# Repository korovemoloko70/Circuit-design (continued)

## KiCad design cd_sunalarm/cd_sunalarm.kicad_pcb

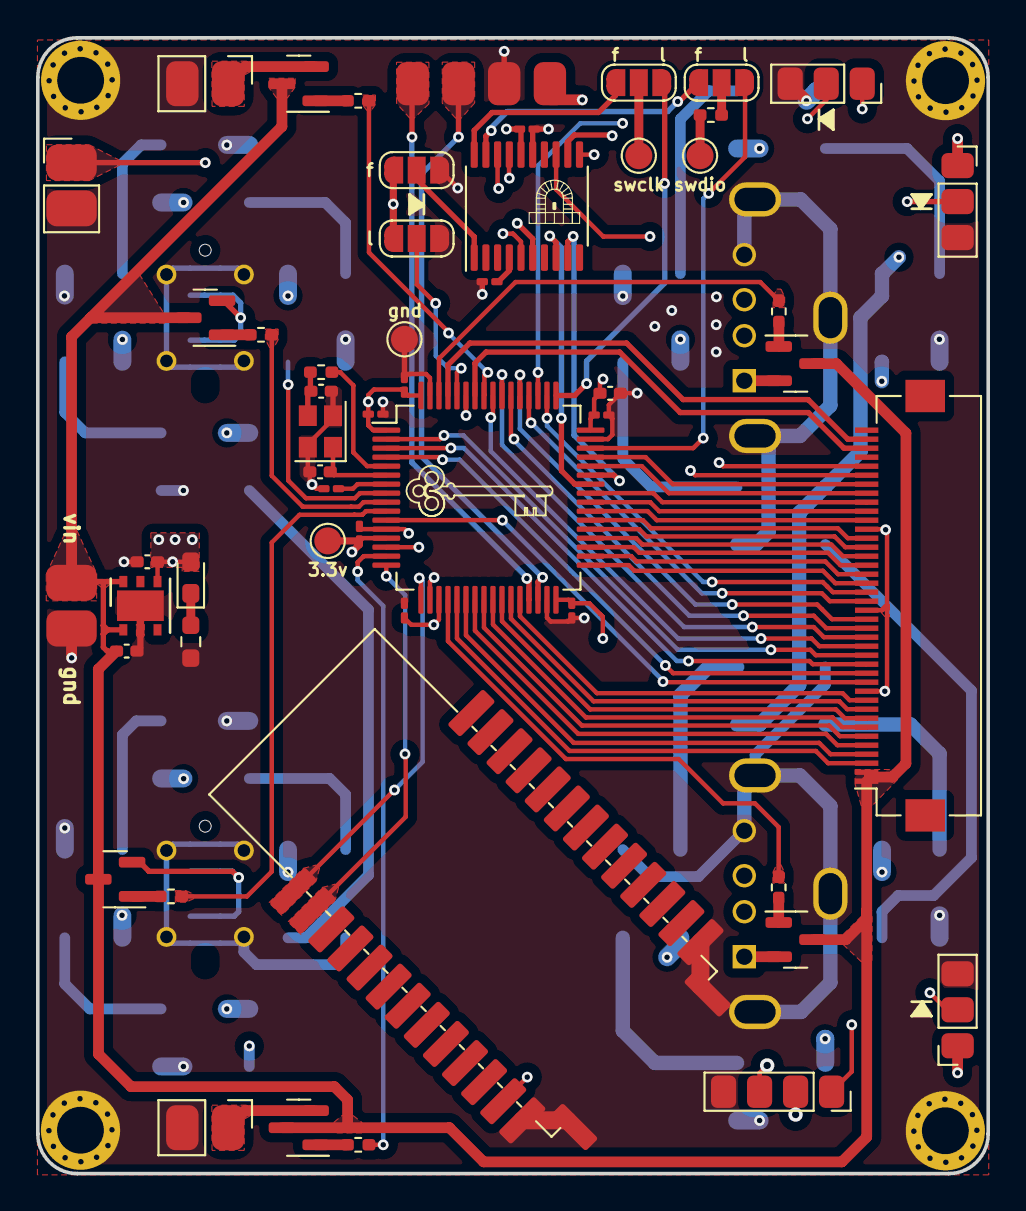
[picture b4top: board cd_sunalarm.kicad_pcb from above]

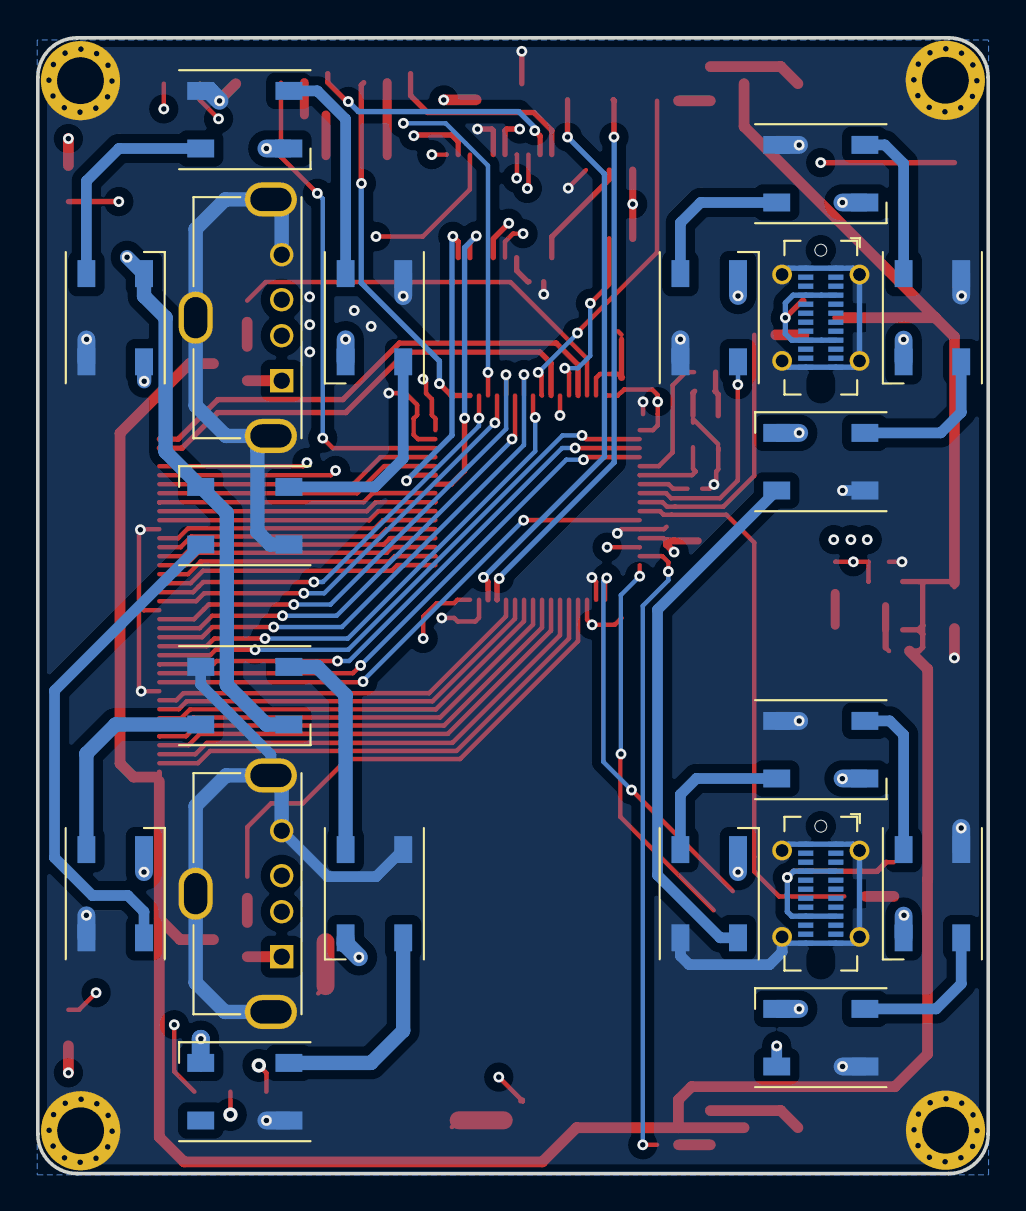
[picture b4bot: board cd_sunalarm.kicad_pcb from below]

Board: 4 copper layers, 52.8 x 63.1 mm, 73 parts (20 on the bottom side), 98 nets.

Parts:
C1: 4u7; C_0402_1005Metric_Pad0.74x0.62mm_HandSolder
C2, C4: 12p; C_0402_1005Metric_Pad0.74x0.62mm_HandSolder
C3, C5, C6, C7, C8, C9, C11, C12, C13: 100nF; C_0201_0603Metric_Pad0.64x0.40mm_HandSolder
C15, C16: 1uF; C_0402_1005Metric_Pad0.74x0.62mm_HandSolder
D1, D2, D3, D4, D5, D6, D7, D8, D9, D10, D11, D12, D13, D14, D15, D16: WS2812B; LED_SK6812_PLCC4_5.0x5.0mm_P3.2mm
D22: green; LED_0603_1608Metric_Pad1.05x0.95mm_HandSolder
J1: Display; Hirose_FH12-40S-0.5SH_1x40-1MP_P0.50mm_Horizontal
J2, J3, J12: Conn_01x03_Female; PinSocket_1x03_P2.00mm_Vertical
J4: temperature; PinSocket_1x04_P2.54mm_Vertical
J5, J6: USB_A; USB_A_Molex_105057_Vertical
J7: WiCh; PinHeader_1x02_P2.54mm_Vertical
J8: Dif; PinHeader_1x02_P2.54mm_Vertical
J9: LED; PinHeader_1x02_P2.54mm_Vertical
J10: power; PinSocket_1x02_P2.54mm_Vertical
J11: sound; PinSocket_1x04_P2.00mm_Vertical
JP1, JP2, JP3, JP4: SolderJumper_3_Open; SolderJumper-3_P1.3mm_Open_RoundedPad1.0x1.5mm
P1, P2: USB_C_Plug_USB2.0; USB_C_Receptacle_GCT_USB4115-03-C
Q2, Q3, Q4, Q5, Q6, Q7: Q_NPN_BEC; SOT-23
R1: 0; R_0402_1005Metric_Pad0.72x0.64mm_HandSolder
R3: 47; R_0402_1005Metric_Pad0.72x0.64mm_HandSolder
R8, R10, R11, R12, R13, R14: 220; R_0402_1005Metric_Pad0.72x0.64mm_HandSolder
R15: 1k; R_0603_1608Metric_Pad0.98x0.95mm_HandSolder
TP1, TP2, TP3, TP4: TestPoint_Small; TestPoint_Pad_D1.5mm
U1: STM32F031F4Px; TSSOP-20_4.4x6.5mm_P0.65mm
U2: STM32L476RCTx; LQFP-64_10x10mm_P0.5mm
U3: HM-10; Bluetooth
U4: LD39050PU33R; DFN-6-1EP_3x3mm_P0.95mm_EP1.7x2.6mm
Y1: 16MHz; Crystal_SMD_2520-4Pin_2.5x2.0mm

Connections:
+3V3: C1.1, C5.1, C6.1, C7.1, C9.1, C11.1, C12.1, C13.1, C16.1, D1.1 (VDD), D2.1 (VDD), D3.1 (VDD), D4.1 (VDD), D5.1 (VDD), D6.1 (VDD), D7.1 (VDD), D8.1 (VDD), D9.1 (VDD), D10.1 (VDD), D11.1 (VDD), D12.1 (VDD), D13.1 (VDD), D14.1 (VDD), D15.1 (VDD), D16.1 (VDD), D22.2 (A), J2.1, J3.1, J4.1, J12.1, JP3.1 (A), JP4.1 (A), TP1.1, U1.5 (VDDA), U1.16 (VDD), U2.1 (VBAT), U2.13 (VDDA), U2.19 (VDD), U2.32 (VDD), U2.48 (VDDUSB), U2.64 (VDD), U3.12 (VCC), U4.4 (VOUT)
+5V: C15.1, J1.1, J1.2, J10.1, Q2.3 (C), Q3.3 (C), Q4.3 (C), Q5.3 (C), Q6.3 (C), Q7.3 (C), U4.1 (EN), U4.6 (VIN)
/NRST_F: C3.1, U1.4 (NRST)
/NRST_L: C8.2, U2.7 (NRST)
B0: J1.21, U2.52 (PC11)
B1: J1.22, U2.50 (PA15)
B2: J1.23, U2.33 (PB12)
B3: J1.24, U2.34 (PB13)
B4: J1.25, U2.35 (PB14)
B5: J1.26, U2.36 (PB15)
B6: J1.27, U2.37 (PC6)
B7: J1.28, U2.38 (PC7)
BL_CTR: J1.34, U2.45 (PA12)
BOOT0_F: JP4.2 (C), U1.1 (BOOT0)
BOOT0_L: JP3.2 (C), U2.60 (BOOT0)
B_RX: U2.16 (PA2), U3.2 (UART_RX)
B_TX: U2.17 (PA3), U3.1 (UART_TX)
CTP_INT: J1.39, U2.61 (PB8)
CTP_RST: J1.35, U2.14 (PA0)
CTP_SCL: J1.38, U2.58 (PB6)
CTP_SDA: J1.36, U2.59 (PB7)
DCLK: J1.30, U2.39 (PC8)
DEN: J1.33, U2.44 (PA11)
DIN: D1.4 (DIN), U2.8 (PC0)
Dif: J8.1, Q2.2 (E)
G0: J1.12, U2.11 (PC3)
G1: J1.13, U2.4 (PC15)
G2: J1.14, U2.3 (PC14)
G3: J1.15, U2.2 (PC13)
G4: J1.16, U2.56 (PB4)
G5: J1.17, U2.55 (PB3)
G6: J1.18, U2.54 (PD2)
G7: J1.19, U2.53 (PC12)
GND: C1.2, C2.2, C3.2, C4.2, C5.2, C6.2, C7.2, C8.1, C9.2, C11.2, C12.2, C13.2, C15.2, C16.2, D1.3 (VSS), D2.3 (VSS), D3.3 (VSS), D4.3 (VSS), D5.3 (VSS), D6.3 (VSS), D7.3 (VSS), D8.3 (VSS), D9.3 (VSS), D10.3 (VSS), D11.3 (VSS), D12.3 (VSS), D13.3 (VSS), D14.3 (VSS), D15.3 (VSS), D16.3 (VSS), J1.11, J1.20, J1.29, J2.3, J3.3, J4.2, J5.4 (GND), J5.5 (Shield), J6.4 (GND), J6.5 (Shield), J7.2, J8.2, J9.2, J10.2, J11.4, J12.3, JP3.3 (B), JP4.3 (B), P1.A1 (GND), P1.A12 (GND), P1.B1 (GND), P1.B12 (GND), P1.S1 (SHIELD), P2.A1 (GND), P2.A12 (GND), P2.B1 (GND), P2.B12 (GND), P2.S1 (SHIELD), R15.2, TP2.1, U1.15 (VSS), U2.12 (VSSA), U2.18 (VSS), U2.31 (VSS), U2.47 (VSS), U2.63 (VSS), U3.13 (GND), U3.14 (GND), U3.21 (GND), U3.22 (GND), U4.2 (GND), U4.7, Y1.2, Y1.4
HSYNC: J1.31, U2.40 (PC9)
LED: J9.1, U1.6 (PA0)
L_IN: J11.3, U1.18 (PA10)
Light1: J2.2, U1.11 (PA5)
Light2: J3.2, U1.12 (PA6)
MIC: J12.2, U2.51 (PC10)
unnamed: C4.1, R3.2, Y1.3
unnamed: D1.2 (DOUT), D2.4 (DIN)
unnamed: D2.2 (DOUT), D3.4 (DIN)
unnamed: D3.2 (DOUT), D4.4 (DIN)
unnamed: D4.2 (DOUT), D5.4 (DIN)
unnamed: D5.2 (DOUT), D6.4 (DIN)
unnamed: D6.2 (DOUT), D7.4 (DIN)
unnamed: D7.2 (DOUT), D8.4 (DIN)
unnamed: D8.2 (DOUT), D9.4 (DIN)
unnamed: D10.2 (DOUT), D11.4 (DIN)
unnamed: D9.2 (DOUT), D10.4 (DIN)
unnamed: D11.2 (DOUT), D12.4 (DIN)
unnamed: D12.2 (DOUT), D13.4 (DIN)
unnamed: D13.2 (DOUT), D14.4 (DIN)
unnamed: D14.2 (DOUT), D15.4 (DIN)
unnamed: D15.2 (DOUT), D16.4 (DIN)
unnamed: D22.1 (K), R15.1
unnamed: JP1.2 (C), R1.2
unnamed: Q2.1 (B), R8.1
unnamed: Q3.1 (B), R10.1
unnamed: Q4.1 (B), R11.1
unnamed: Q5.1 (B), R12.1
unnamed: Q6.1 (B), R13.1
unnamed: Q7.1 (B), R14.1
OCS_IN: C2.1, U2.6 (PH1), Y1.1
OCS_OUT: R3.1, U2.5 (PH0)
R0: J1.3, U2.21 (PA5)
R1: J1.4, U2.22 (PA6)
R2: J1.5, U2.23 (PA7)
R3: J1.6, U2.24 (PC4)
R4: J1.7, U2.25 (PC5)
R5: J1.8, U2.26 (PB0)
R6: J1.9, U2.27 (PB1)
R7: J1.10, U2.28 (PB2)
RX1: U1.9 (PA3), U2.43 (PA10)
R_IN1: J11.1, U1.13 (PA7)
R_IN2: J11.2, U1.17 (PA9)
STMDif: R8.2, U2.57 (PB5)
STMWiCh: R14.2, U2.15 (PA1)
STMusbA1: R12.2, U2.62 (PB9)
STMusbA2: R13.2, U2.20 (PA4)
STMusbC1: R10.2, U2.10 (PC2)
STMusbC2: R11.2, U2.9 (PC1)
SWCLK: JP2.2 (C), TP4.1
SWCLK_F: JP2.1 (A), U1.20 (PA14)
SWCLK_L: JP2.3 (B), U2.49 (PA14)
SWDIO: R1.1, TP3.1
SWDIO_F: JP1.1 (A), U1.19 (PA13)
SWDIO_L: JP1.3 (B), U2.46 (PA13)
TX1: U1.8 (PA2), U2.42 (PA9)
T_SCL: J4.4, U2.29 (PB10)
T_SDA: J4.3, U2.30 (PB11)
VSYNC: J1.32, U2.41 (PA8)
WiCh: J7.1, Q7.2 (E)
usbA1: J5.1 (VBUS), Q5.2 (E)
usbA2: J6.1 (VBUS), Q6.2 (E)
usbC1: P1.A4 (VBUS), P1.A9 (VBUS), P1.B4 (VBUS), P1.B9 (VBUS), Q3.2 (E)
usbC2: P2.A4 (VBUS), P2.A9 (VBUS), P2.B4 (VBUS), P2.B9 (VBUS), Q4.2 (E)

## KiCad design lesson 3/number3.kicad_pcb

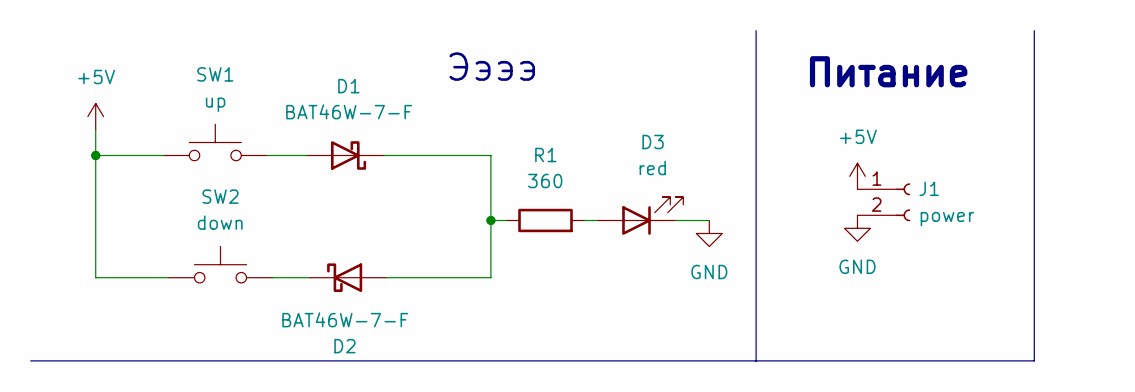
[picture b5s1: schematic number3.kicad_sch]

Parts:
D1, D2: BAT46W-7-F; Nexperia_CFP3_SOD-123W
D3: red; LED_0805_2012Metric_Pad1.15x1.40mm_HandSolder
J1: power; PinSocket_1x02_P2.54mm_Vertical
R1: 360; R_0805_2012Metric_Pad1.20x1.40mm_HandSolder
SW1: up; SW_SPST_TL3342
SW2: down; SW_SPST_TL3342

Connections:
+5V: J1.1, SW1.1, SW2.1
GND: D3.1 (K), J1.2
unnamed: D1.1 (K), D2.2 (A), R1.1
unnamed: D1.2 (A), SW1.2
unnamed: D2.1 (K), SW2.2
unnamed: D3.2 (A), R1.2

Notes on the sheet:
Питание
Ээээ

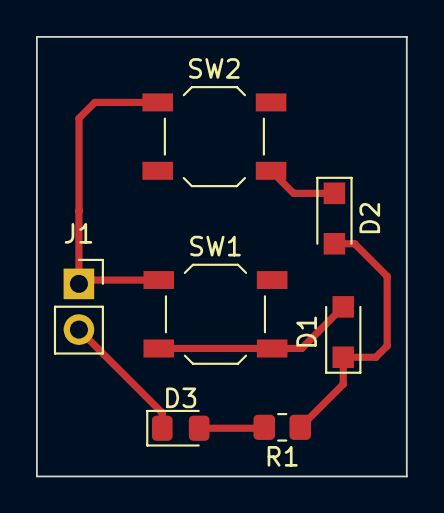
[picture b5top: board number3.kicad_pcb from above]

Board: 2 copper layers, 20.6 x 24.4 mm, 7 parts (0 on the bottom side), 6 nets.

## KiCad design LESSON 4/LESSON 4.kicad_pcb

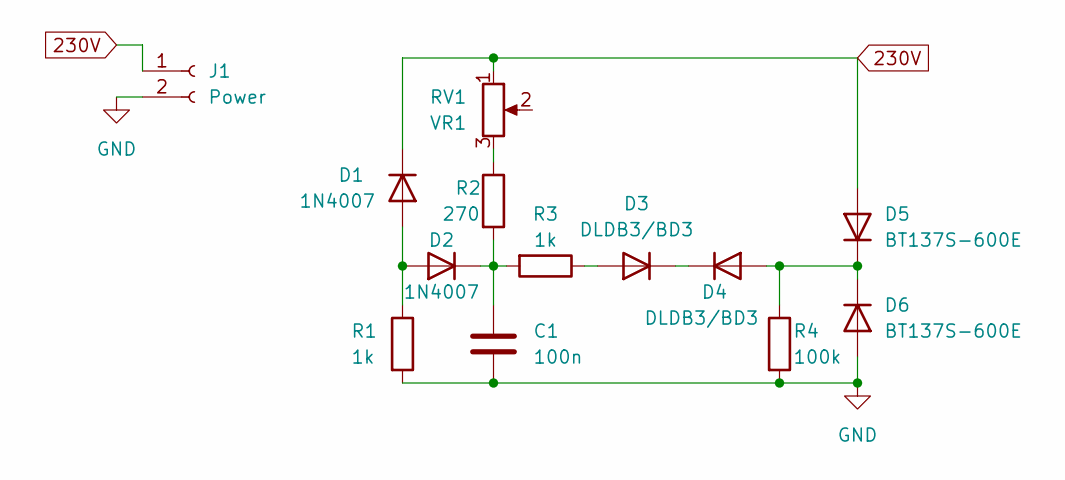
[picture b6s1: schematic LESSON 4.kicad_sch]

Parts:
C1: 100n; C_0805_2012Metric_Pad1.18x1.45mm_HandSolder
D1, D2: 1N4007; D_0603_1608Metric_Pad1.05x0.95mm_HandSolder
D3, D4: DLDB3/BD3; D_0603_1608Metric_Pad1.05x0.95mm_HandSolder
D5, D6: BT137S-600E; D_0603_1608Metric_Pad1.05x0.95mm_HandSolder
J1: Power; PinSocket_2x01_P2.54mm_Vertical
R1: 1k; R_0612_1632Metric_Pad1.18x3.40mm_HandSolder
R2: 270; R_0612_1632Metric_Pad1.18x3.40mm_HandSolder
R3: 1k; R_0603_1608Metric_Pad0.98x0.95mm_HandSolder
R4: 100k; R_01005_0402Metric_Pad0.57x0.30mm_HandSolder
RV1: VR1; Potentiometer_Bourns_3314R-1_Vertical_Hole

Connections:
230V: D1.1 (K), D5.2 (A), J1.1, RV1.1
GND: C1.2, D6.2 (A), J1.2, R1.2, R4.2
unnamed: C1.1, D2.1 (K), R2.2, R3.2
unnamed: D1.2 (A), D2.2 (A), R1.1
unnamed: D3.1 (K), D4.1 (K)
unnamed: D3.2 (A), R3.1
unnamed: D4.2 (A), D5.1 (K), D6.1 (K), R4.1
unnamed: R2.1, RV1.3

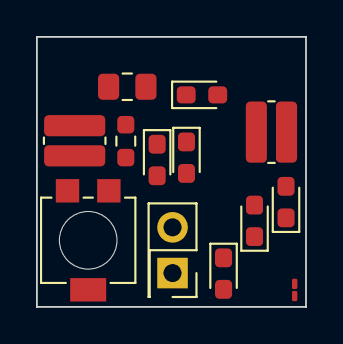
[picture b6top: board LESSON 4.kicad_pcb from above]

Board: 2 copper layers, 15.0 x 15.0 mm, 13 parts (0 on the bottom side), 8 nets.

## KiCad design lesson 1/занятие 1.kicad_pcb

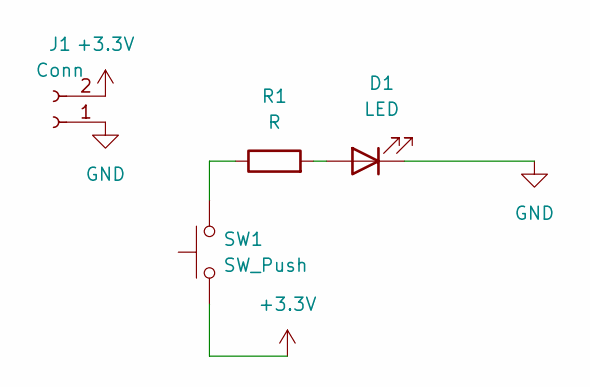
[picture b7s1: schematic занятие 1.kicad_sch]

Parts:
D1: LED; D_0603_1608Metric_Pad1.05x0.95mm_HandSolder
J1: Conn; PinSocket_2x01_P2.54mm_Vertical
R1: R; R_0805_2012Metric_Pad1.20x1.40mm_HandSolder
SW1: SW_Push; SW_SPST_TL3305B

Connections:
+3.3V: J1.2, SW1.1
GND: D1.1 (K), J1.1
unnamed: D1.2 (A), R1.2
unnamed: R1.1, SW1.2

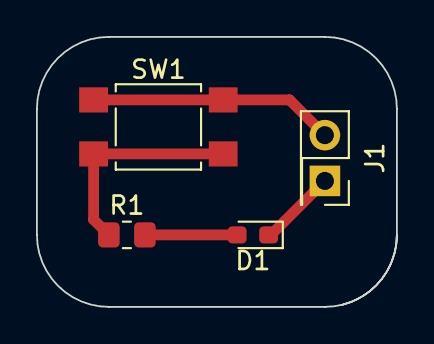
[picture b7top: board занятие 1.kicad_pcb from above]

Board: 2 copper layers, 20.0 x 15.0 mm, 4 parts (0 on the bottom side), 4 nets.

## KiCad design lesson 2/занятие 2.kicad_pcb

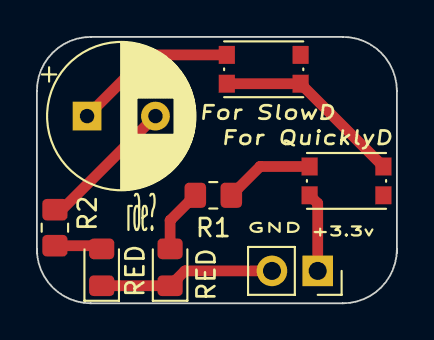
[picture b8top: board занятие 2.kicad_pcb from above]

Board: 2 copper layers, 20.0 x 14.8 mm, 8 parts (0 on the bottom side), 7 nets.

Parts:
C1: 100mF; CP_Radial_D8.0mm_P3.80mm
D1, D2: RED; D_0805_2012Metric_Pad1.15x1.40mm_HandSolder
J1: Conn_01x02_Female; PinSocket_1x02_P2.54mm_Vertical
R1, R2: 20; R_0805_2012Metric_Pad1.20x1.40mm_HandSolder
SW1: For QuicklyD; SW_Push_1P1T_NO_CK_KMR2
SW2: For SlowD; SW_Push_1P1T_NO_CK_KMR2

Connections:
+3.3V: J1.1, SW1.1
GND: D1.1 (K), D2.1 (K), J1.2
unnamed: D1.2 (A), R1.1
unnamed: D2.2 (A), R2.2
unnamed: R1.2, SW1.2, SW2.1
unnamed: C1.2, R2.1
unnamed: C1.1, SW2.2

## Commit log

2026-05-03 Первый коммит: добавлены проекты KiCad
